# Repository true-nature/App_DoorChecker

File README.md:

App_DoorChecker
===============

The wireless monitor of the door lock up status.
It works on ToCoS TWE-Lite.

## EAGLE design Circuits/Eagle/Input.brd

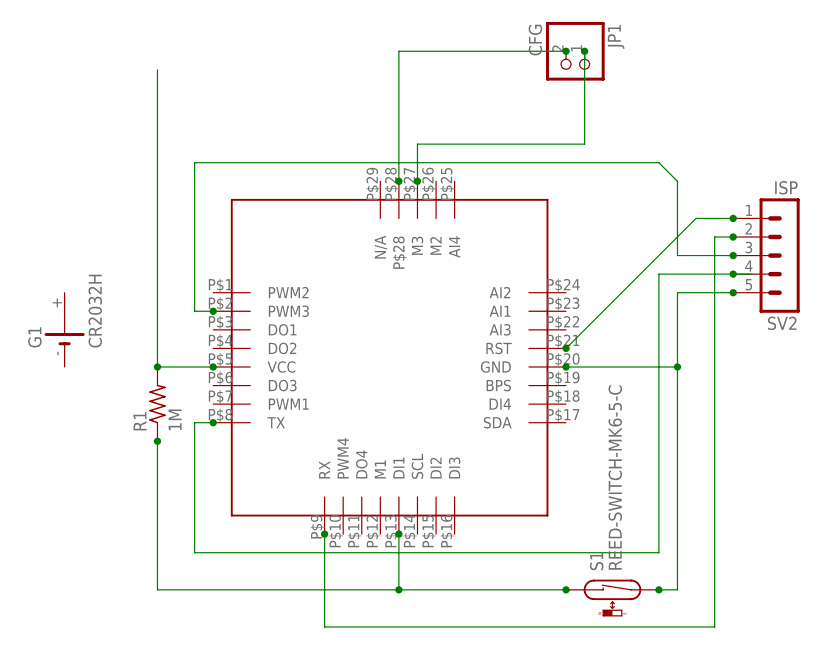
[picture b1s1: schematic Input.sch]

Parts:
G1: CR2032H
JP1: CFG; 1X02
R1: 1M; V234/12
S1: REED-SWITCH-MK6-5-C; MK6-5
SV2: ISP; MA05-1
U$1: LITE

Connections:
unnamed: SV2.1, U$1.P$21 (RST)
unnamed: R1.2, U$1.P$5 (VCC)
unnamed: R1.1, S1.1, U$1.P$13 (DI1)
unnamed: S1.2, SV2.5, U$1.P$20 (GND)
unnamed: SV2.2, U$1.P$9 (RX)
unnamed: SV2.3, U$1.P$2 (PWM3)
unnamed: SV2.4, U$1.P$8 (TX)
unnamed: JP1.1, U$1.P$27 (M3)
unnamed: JP1.2, U$1.P$28

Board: 2 copper layers, 6 parts (0 on the bottom side), 9 nets, no tracks yet.

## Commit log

2014-09-25 Ignore firmware binaries.
2014-09-25 Updated project description.
2014-09-25 Imported from Samp_Monitor v1.3.2 project.
2014-09-25 Updated to Samp_Monitor v1.3.3.
2014-09-25 Changed application name.
2014-09-25 Eclipseのコード解釈エラーを解決。
2014-09-25 プルアップ停止判定のタイミングを確認するToDoタスクを追加。
2014-09-25 Making up a ToDo list.
2014-09-26 ToDo項目をリストアップ中。
2014-09-26 readmeの中身を改造後の予定動作に差し替え。
2014-09-26 EEPROM読み込み前では設定値がプルアップ判定に反映されないので、読み込み後に移動。
2014-09-27 Eclipseのコード解釈エラーを解消。
2014-09-27 子機のドアアラームを無効化。定期的に状態送信を有効化。
2014-09-27 App_Twelite v1.7の実験的な実装からI2C接続LCDのコードをコピー。
2014-09-27 I2C LCD functions are ready to call.
2014-09-27 子機の数をEEPROMに記憶。
2014-09-27 実装が済んだToDoのマークアップを削除。
2014-09-28 子機使用状況を最大数でなく使用IDのマスクで管理する。
2014-09-28 ADCを有効にして電源電圧をモニターする。
2014-09-28 32bit all 1は特異値なので使用不可。ビット数を減らして子機は最大30とする。
2014-09-28 flash.cがconfig.hをincludeしないので無条件でフィールド追加。
2014-09-28 u32idmaskは0にできない。
2014-09-28 パケット受信時にスイッチ状態、子機ID,電源電圧を保存。
2014-09-28 配列の先頭から使用する。
2014-09-28 2行8桁のLCDで表示できる数に制限。
2014-09-28 I2C LCD(AQM0802A)でステータスを表示する。
2014-09-28 通信途絶の場合は低電圧と同じ表示。
2014-09-29 Designing the circuit.
2014-09-29 Revert "子機のドアアラームを無効化。定期的に状態送信を有効化。"
    This reverts commit 1dabc5c033cbefd2f427b25f9b8f2b4ddbc21269.
    Conflicts:
    Common/Source_User/config.h
    EndDevice_Input/Source/ProcessEv_Door_Timer.c
2014-09-29 子機モード51からFEへ軌道変更。
2014-09-29 PKT_ID_BOTTON用に変更中。
2014-09-29 tsRxPktInfoをアドレス私に変更。
2014-09-29 子機モード0x51(PKT_ID_BOTTON)を定時送信化して戸締りチェッカー再実装。
2014-09-29 Moved I2C_impl to Common. Endpoint_Remote will use it.
2014-09-30 機能別に回路図をInput,Parent,Remoteの3部構成とする。
2014-09-30 確認UIをParentからRemoteへ移動。
2014-09-30 ToDoをParentからRempoteへ引っ越し。
2014-09-30 AQM0802Aへの状態表示をParentからRemoteへ移植。
2014-09-30 Moved circuit design data.
2014-09-30 AppIdを親機候補のSerial No.ベースに変更。 戸締り情報をMessagePoolに乗せてRemoteで表示できるようになった。
2014-09-30 Remote起動時にLCD初期化。
2014-09-30 16台目の子機が表示されないバグを修正。
2014-09-30 備忘録をToDoに追加。
2014-09-30 LCD(AQM0802A)のGNDをFETでスイッチする。
2014-10-01 ParentからI2C LCD表示を削除。
2014-10-01 RemoteのPWM1,2,4で電源、窓開け、通信のエラー状態を表示。
2014-10-01 電池駆動でも読めるコントラストに調整。
2014-10-01 LEDをsink制御に変更。
2014-10-01 LED表示を数秒間継続。スリープ時に消灯。
2014-10-01 子機再登録モードのToDoを追加。
2014-10-01 LCDをACM1602に変更。
2014-10-01 基板レイアウトをPaasで作成してみる。
2014-10-01 親機にLEDと圧電スピーカーを追加。
2014-10-02 実体配線図を作成。
2014-10-02 SLEEP#のプルアップを停止。
2014-10-03 予定動作の説明を、ボタン起動モード、リモート子機を含む三部構成に変更。
2014-10-03 DO3でLCTとATPの電源を制御。DI2で音声再生の終了待ち確認。
2014-10-03 Q1の保護ダイオードを追加。Q2は寄生ダイオードが内蔵されているので不要。
2014-10-03 音声合成の枠組みだけ作成。
2014-10-04 SMOD0接地、PLAYをDI3で検出。
2014-10-04 ATP3012を使用した音声案内を実装。
2014-10-04 memccpy()の用法ミスを修正。
2014-10-04 基板名を付加
2014-10-04 デバッグ用のprintを削除。
2014-10-05 イントネーション修正、デバッグprint削除。
2014-10-06 3.3V電源はDC StepUpコンバータで昇圧供給。
2014-10-06 メッセージ数可変方式に変更。 PLAY検出ではbusyの代用にならないので、ポーリングでATPのbusyを確認する。
2014-10-06 ATP301xへのリセットを追加。PLAY/への結線を廃止。
2014-10-06 DC昇圧モジュール名にHT7733A moduleを採用。
2014-10-06 AKI B基板で作る予定は無くなった。
2014-10-06 HT7733A 昇圧型ＤＣＤＣコンバータ ＳｔｅｐＵＰ・ＤＩＰをライブラリに追加。
2014-10-07 EDLCの単位間違いを修正。
2014-10-07 圧電スピーカーにダイオードを接続。
2014-10-07 Speakerの＋側をHT7733Aから供給。
2014-10-07 問題なく動作する部分のToDoコメントを削除。
2014-10-07 表示中の再生中断とMessagePool再要求を可能にする。
2014-10-07 Endpoint_InputからADCコードを移植中。
2014-10-07 Abortは応答を待たない。
2014-10-07 ADC初期化失敗するので保留。 ACM1602も接続。
2014-10-07 不要になった受信バッファを削除。
2014-10-07 WarmStartでADCが初期化されないバグを修正。
2014-10-07 Remote子機の電圧チェックが動作。表示は未完。
2014-10-07 窓以外の通信エラーと電池警告の表示をToDoにメモ。
2014-10-08 表示中の再問い合わせ、Remote子機電池残量チェックを実装したのでToDo削除。
2014-10-09 Removed unused variable.
2014-10-09 ACM1602の2行目にメッセージ文字列を表示。 親機通信エラーは1行目にもメッセージ表示。
2014-10-09 Designing PCB.
2014-10-10 カタカナがUTF-8でエンコードされていたバグを修正。
2014-10-11 ADCを待ってから表示開始。再スタート時にADCも再計測。
2014-10-11 DCコンバータを実体配線図に追加。
2014-10-12 正常時にRemote子機自身の電圧を表示。 電源は液晶のバックライトで確認できるため、正常時はLED点灯無し。 LED配置換え。
2014-10-12 M2の結線位置を訂正。
2014-10-12 電池残量警告のｲﾝﾃﾞｯｸｽ名を修正。
2014-10-13 KiCAD,EAGLEでのPCB設計を試行中。
2014-10-13 LCDでも3.3V電源を使用するため、音声合成はATP3011でなくATP3012で確定。
2014-10-13 TWE-Lite SMDのフットプリントをデータシートから作成中。
2014-10-14 TWE-Lite SMDのパッド位置修正、外形線追加。
2014-10-14 TWE-EH版のセンサー子機回路図を追加。
2014-10-15 タカチCST-2032をライブラリに追加(名前だけ)。
2014-10-16 CST-2032のスルーホール位置を決定。
2014-10-16 結線用スルーホール追加。
2014-10-20 コピー結果が化けるので、S_OCTET(G_OCTET())の羅列をmemcpy()に置き換えた。
2014-10-21 Fixed typo.
2014-10-21 出力がUartモードの場合もpRxPktInfoのメンバに受信した値をセットする。
2014-10-21 TWE-EH Solar版回路図を差し替え。
2014-10-21 M2をGNDと隣接するCFG#コネクタへ接続。
2014-10-23 Increased expiration timeout from 1 to 3 minutes.
2014-10-25 Router動作中にPWM4に接続したLEDを点滅させる。
2014-11-02 ボタン状態に応じて割り込みエッジを選択する。
2014-11-02 Eagleデータは不要。
2014-11-03 HT82V739,ATP3011を使う回路図を作成。
2014-11-04 Fixed pin no of DC Step Up Converter.
2014-11-04 Fixed pin no of HT82V739.
2014-11-04 ATP3011版の実体配線図を追加。
2014-11-04 アナログセンサ用の転記処理を修正。
2014-11-05 ATP3011版の実体配線図完成。
2014-11-05 回路図画像を追加。
2014-11-06 ATP3011のGNDを配線。LCD電源の配線統合を反映。
2014-11-11 書き換え用ピンヘッダを7ピンに修正。
2014-11-16 Added scripts for Raspberry Pi.
2014-11-16 Added MRTG configuration.
2014-11-25 Read mail addresses from config file.
2014-12-09 ERC checked.
2014-12-09 Vcc,GNDラインにラベル追加。
2014-12-24 Updated KiCAD data.
2014-12-25 ERC passed.
2015-01-18 Copied libraries from BicycleFinder.
2015-01-19 Assigned PBCS-75 as battery holder.
2015-01-19 Added small EDLC module.
2015-01-20 Use chip registers.
2015-01-20 Creating 3D model of CS-75 plastic case.
2015-01-21 Moved BSch3V data to subdirectory.
2015-01-21 Renamed directory.
2015-01-21 Moved libraries to ../kicad-twe.
2015-01-21 Added 3D model of pinheader.
2015-01-21 Created KiCAD project for DoorChecker Remote.
2015-01-21 Fixed: Reed switch was not connected to GND.
2015-01-22 Added DC-DC converter module.
2015-01-23 Copied schematic diagram from BSch3V to KiCAD.
2015-01-23 Assigned footprint.
2015-01-23 Consider NTH.
2015-01-25 Modified parts layout.
2015-01-25 Replaced RV2 to RV-3362P.
2015-01-25 Renamed RV-TSR-3386T.
2015-01-26 Changed PCB thickness.
2015-01-27 Updated 3D model.
2015-01-27 Moved ATP.
2015-01-27 Re-layout by FreeRouting.
2015-01-28 Moved LED out of the PCB via pin header.
2015-01-29 Set inhibit area under CR2032.
2015-01-29 Replaced footprint of TWE-Lite SMD with antenna hole.
2015-01-29 Supply 2/3 divided volt to adc2.
2015-01-30 Moved silk position.
2015-01-31 Ordered to PCB prototyping service.
2015-02-01 Removed BOM list.
2015-02-06 Moved location of 3D models.
2015-02-23 Replaced a EDLC to an array of MLCC.
2015-02-26 Added 3D model of ACM1602NI LCD.
2015-03-01 Store WakeUpByButton field after flash load.
2015-03-02 Added a voltage monitor.
2015-03-07 Show door status in rain notification.
2015-03-08 Fixed: Switch to configuration mode by M2.
2015-03-08 Changed register value from 75 to 1k.
2015-03-15 Merged raw dump into parsed output file.
2015-03-16 Use both M2 and M3 for configuration switch.
2015-03-16 Start to edit current KiCad.
2015-03-22 Modified reset circuit.
2015-03-23 Migrating to current version of KiCad.
2015-03-28 Changed library file name from TWE-Lite to favorites.
2015-04-26 Limit rain alert frequency less than one per an hour.
2015-05-09 Fixed: Dump file was not saved.
2015-10-19 Simplified power supply block.
2015-10-26 Turn off the LED connected to DO1.
2015-11-29 Added email filter program to fetch door status.
2015-11-29 Updated library list.
2016-04-18 Changed location of 3d shapes.
2016-05-02 Added the monitor script for TWE-Lite 2525A.
2016-05-09 Replaced the FET symbol.
2017-01-22 Catch exception thrown by binascii.unhexlify().
2017-01-25 Identify rain sensor by Logical Id.
2017-06-17 Fixed format string.
2017-06-17 Fixed octal number.
2017-06-17 Read serial data as bytes.
2017-06-17 Migrated to Python3.
2018-01-03 雨センサー基板を作成
2018-02-14 Updated libraries
2018-02-14 Replaced SMD by DIP
2018-02-15 Replaced sensor to pinheader
2018-03-07 Migrating to KiCad 5.0
2018-03-09 Removed rescue library
2018-03-14 Updated footprint
2018-03-19 Updated symbols
2018-03-21 ADC2をGNDに配線
2018-03-26 Updated symbol of TWELITE
2019-03-23 Break when an exception has caught
2019-03-30 Updated by working script
